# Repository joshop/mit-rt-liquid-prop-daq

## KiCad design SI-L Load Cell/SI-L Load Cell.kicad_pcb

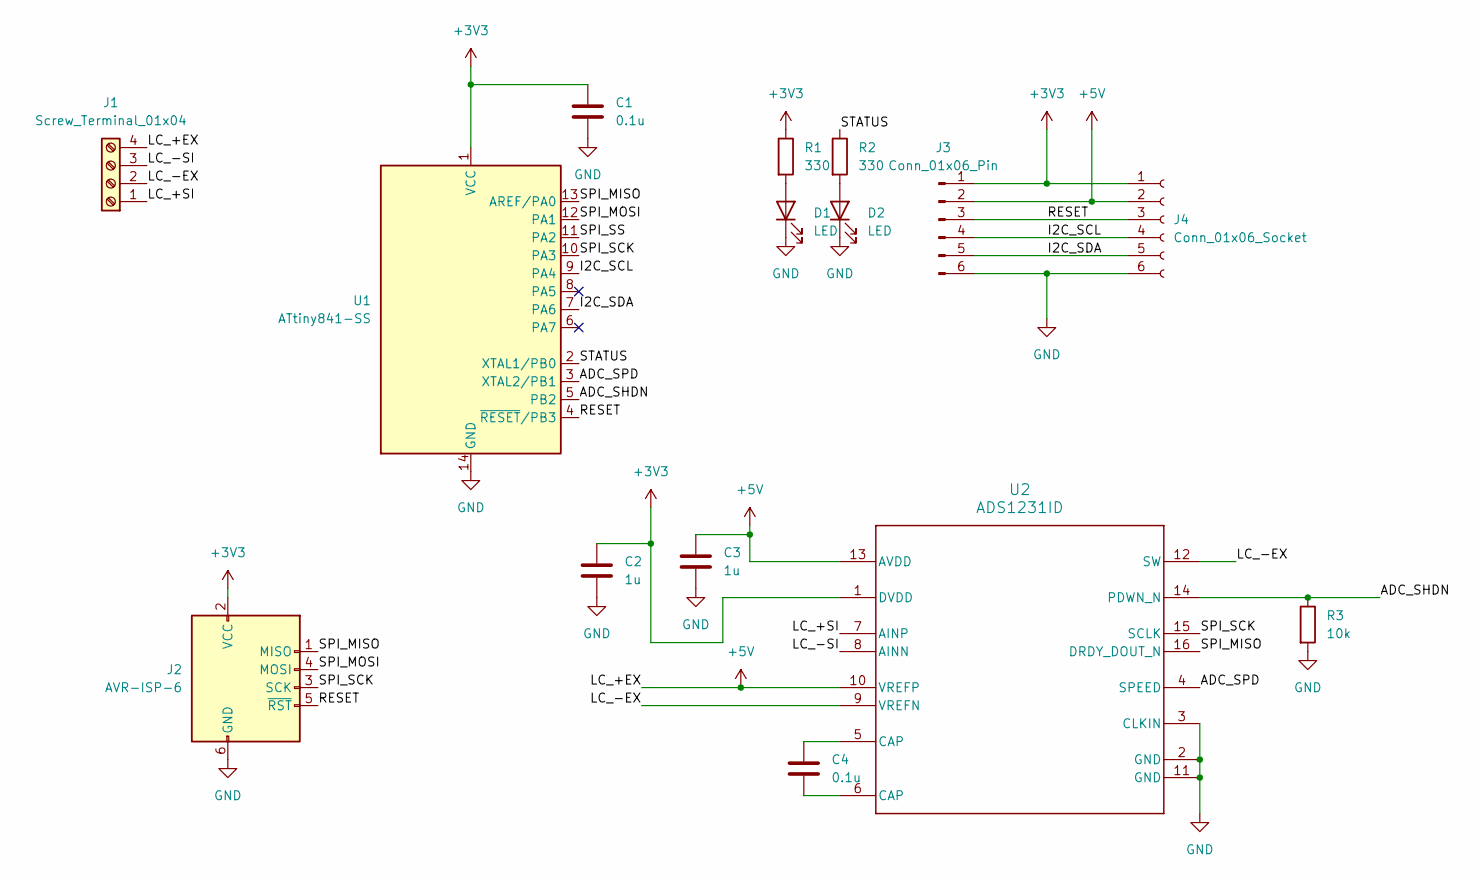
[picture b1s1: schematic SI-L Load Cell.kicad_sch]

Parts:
C1, C4: 0.1u; C_0603_1608Metric
C2, C3: 1u; C_0603_1608Metric
D1, D2: LED; LED_0603_1608Metric
J1: Screw_Terminal_01x04; TerminalBlock_Phoenix_MPT-0,5-4-2.54_1x04_P2.54mm_Horizontal
J2: AVR-ISP-6; Tag-Connect_TC2030-IDC-NL_2x03_P1.27mm_Vertical
J3: Conn_01x06_Pin; PinHeader_1x06_P2.54mm_Horizontal
J4: Conn_01x06_Socket; PinSocket_1x06_P2.54mm_Horizontal
R1, R2: 330; R_0603_1608Metric
R3: 10k; R_0603_1608Metric
U1: ATtiny841-SS; SOIC-14_3.9x8.7mm_P1.27mm
U2: ADS1231ID; D0016A_N

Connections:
+3V3: C1.1, C2.1, J2.2 (VCC), J3.1, J4.1, R1.1, U1.1 (VCC), U2.1 (DVDD)
+5V: C3.1, J1.4, J3.2, J4.2, U2.10 (VREFP), U2.13 (AVDD)
/ADC_SHDN: R3.1, U1.5 (PB2), U2.14 (PDWN_N)
/ADC_SPD: U1.3 (XTAL2/PB1), U2.4 (SPEED)
/I2C_SCL: J3.4, J4.4, U1.9 (PA4)
/I2C_SDA: J3.5, J4.5, U1.7 (PA6)
/LC_+SI: J1.1, U2.7 (AINP)
/LC_-EX: J1.2, U2.9 (VREFN), U2.12 (SW)
/LC_-SI: J1.3, U2.8 (AINN)
/RESET: J2.5 (~RST), J3.3, J4.3, U1.4 (~RESET/PB3)
/SPI_MISO: J2.1 (MISO), U1.13 (AREF/PA0), U2.16 (DRDY_DOUT_N)
/SPI_MOSI: J2.4 (MOSI), U1.12 (PA1)
/SPI_SCK: J2.3 (SCK), U1.10 (PA3), U2.15 (SCLK)
/SPI_SS: U1.11 (PA2)
/STATUS: R2.1, U1.2 (XTAL1/PB0)
GND: C1.2, C2.2, C3.2, D1.1 (K), D2.1 (K), J2.6 (GND), J3.6, J4.6, R3.2, U1.14 (GND), U2.2 (GND), U2.3 (CLKIN), U2.11 (GND)
unnamed: C4.1, U2.5 (CAP)
unnamed: C4.2, U2.6 (CAP)
unnamed: D1.2 (A), R1.2
unnamed: D2.2 (A), R2.2

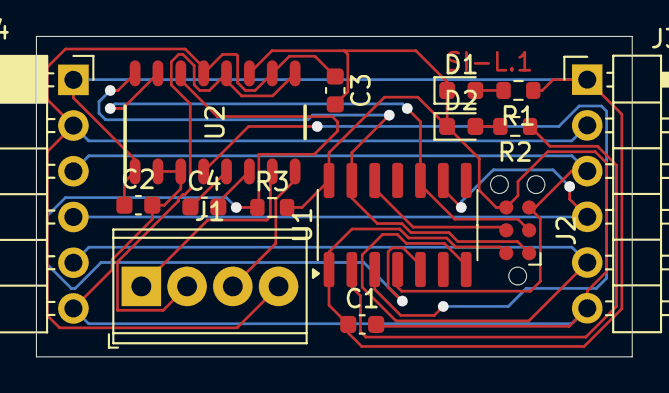
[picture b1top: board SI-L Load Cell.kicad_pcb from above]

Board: 2 copper layers, 33.1 x 17.8 mm, 15 parts (0 on the bottom side), 19 nets.

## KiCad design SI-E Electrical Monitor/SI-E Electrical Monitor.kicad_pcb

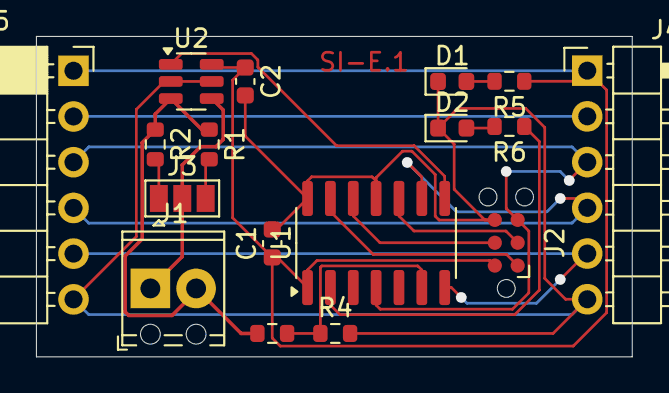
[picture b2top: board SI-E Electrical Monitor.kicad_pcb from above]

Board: 2 copper layers, 33.1 x 17.8 mm, 17 parts (0 on the bottom side), 18 nets.

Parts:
C1: 0.1u; C_0603_1608Metric
C2: C; C_0603_1608Metric
D1, D2: LED; LED_0603_1608Metric
J1: Screw_Terminal_01x02; TerminalBlock_Phoenix_MPT-0,5-2-2.54_1x02_P2.54mm_Horizontal
J2: AVR-ISP-6; Tag-Connect_TC2030-IDC-NL_2x03_P1.27mm_Vertical
J3: Conn_01x03; SolderJumper-3_P1.3mm_Open_Pad1.0x1.5mm
J4: Conn_01x06_Pin; PinHeader_1x06_P2.54mm_Horizontal
J5: Conn_01x06_Socket; PinSocket_1x06_P2.54mm_Horizontal
R1: 3m; R_0603_1608Metric
R2: 30m; R_0603_1608Metric
R3: 33k; R_0603_1608Metric
R4: 11k; R_0603_1608Metric
R5, R6: 330; R_0603_1608Metric
U1: ATtiny841-SS; SOIC-14_3.9x8.7mm_P1.27mm
U2: INA181; SOT-23-6

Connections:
+3V3: C1.1, C2.1, J2.2 (VCC), J4.1, J5.1, R5.1, U1.1 (VCC), U2.6 (V+)
+5V: J4.2, J5.2
/CS+: J1.2, R1.1, R2.1, R3.1, U2.3 (+)
/CS-: J1.1, J3.2, U2.4 (-)
/CS_OUT: U1.8 (PA5), U2.1
/I2C_SCL: J4.4, J5.4, U1.9 (PA4)
/I2C_SDA: J4.5, J5.5, U1.7 (PA6)
/RESET: J2.5 (~RST), J4.3, J5.3, U1.4 (~RESET/PB3)
/SPI_MISO: J2.1 (MISO), U1.13 (AREF/PA0)
/SPI_MOSI: J2.4 (MOSI), U1.12 (PA1)
/SPI_SCK: J2.3 (SCK), U1.10 (PA3)
/STATUS: R6.1, U1.2 (XTAL1/PB0)
GND: C1.2, C2.2, D1.1 (K), D2.1 (K), J2.6 (GND), J4.6, J5.6, R4.2, U1.11 (PA2), U1.14 (GND), U2.2 (GND), U2.5 (REF)
unnamed: D1.2 (A), R5.2
unnamed: D2.2 (A), R6.2
unnamed: J3.1, R2.2
unnamed: J3.3, R1.2
unnamed: R3.2, R4.1, U1.6 (PA7)

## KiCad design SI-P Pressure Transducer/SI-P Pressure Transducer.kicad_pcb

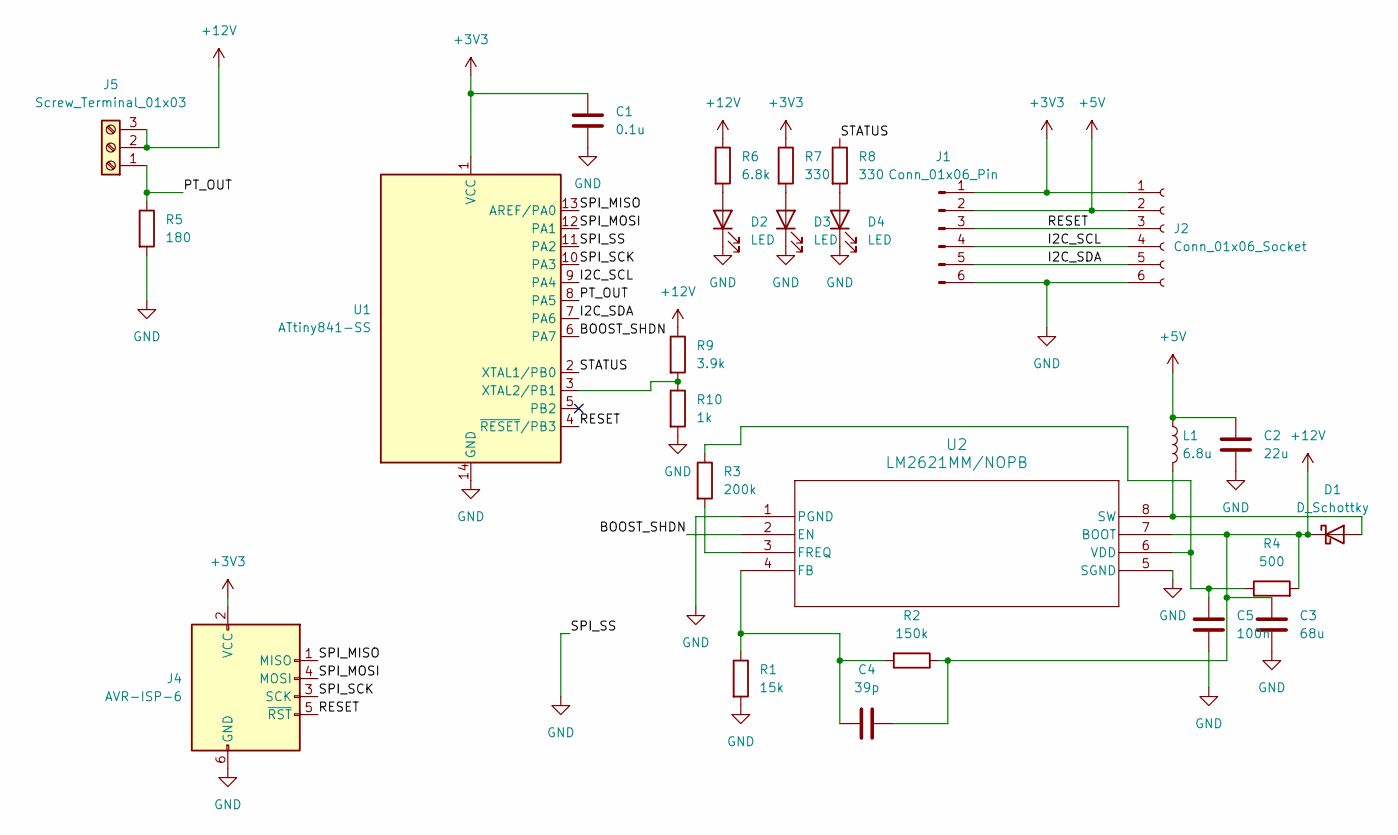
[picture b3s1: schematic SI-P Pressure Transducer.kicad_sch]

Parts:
C1: 0.1u; C_0603_1608Metric
C2: 22u; C_0603_1608Metric
C3: 68u; C_0805_2012Metric
C4: 39p; C_0603_1608Metric
C5: 100n; C_0603_1608Metric
D1: D_Schottky; D_0603_1608Metric
D2, D3, D4: LED; LED_0603_1608Metric
J1: Conn_01x06_Pin; PinHeader_1x06_P2.54mm_Horizontal
J2: Conn_01x06_Socket; PinSocket_1x06_P2.54mm_Horizontal
J4: AVR-ISP-6; Tag-Connect_TC2030-IDC-NL_2x03_P1.27mm_Vertical
J5: Screw_Terminal_01x03; TerminalBlock_Phoenix_MPT-0,5-3-2.54_1x03_P2.54mm_Horizontal
L1: 6.8u; L_0805_2012Metric
R1: 15k; R_0603_1608Metric
R2: 150k; R_0603_1608Metric
R3: 200k; R_0603_1608Metric
R4: 500; R_0603_1608Metric
R5: 180; R_0603_1608Metric
R6: 6.8k; R_0603_1608Metric
R7, R8: 330; R_0603_1608Metric
R9: 3.9k; R_0603_1608Metric
R10: 1k; R_0603_1608Metric
U1: ATtiny841-SS; SOIC-14_3.9x8.7mm_P1.27mm
U2: LM2621MM/NOPB; VSSOP-8_3x3mm_P0.65mm

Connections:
+3V3: C1.1, J1.1, J2.1, J4.2 (VCC), R7.1, U1.1 (VCC)
+5V: C2.1, J1.2, J2.2, L1.1
+12V: C3.1, C4.1, D1.1 (K), J5.2, J5.3, R2.1, R4.2, R6.1, R9.1, U2.7 (BOOT)
/BOOST_SHDN: U1.6 (PA7), U2.2 (EN)
/I2C_SCL: J1.4, J2.4, U1.9 (PA4)
/I2C_SDA: J1.5, J2.5, U1.7 (PA6)
/PT_OUT: J5.1, R5.1, U1.8 (PA5)
/RESET: J1.3, J2.3, J4.5 (~RST), U1.4 (~RESET/PB3)
/SPI_MISO: J4.1 (MISO), U1.13 (AREF/PA0)
/SPI_MOSI: J4.4 (MOSI), U1.12 (PA1)
/SPI_SCK: J4.3 (SCK), U1.10 (PA3)
/STATUS: R8.1, U1.2 (XTAL1/PB0)
GND: C1.2, C2.2, C3.2, C5.2, D2.1 (K), D3.1 (K), D4.1 (K), J1.6, J2.6, J4.6 (GND), R1.2, R5.2, R10.2, U1.11 (PA2), U1.14 (GND), U2.1 (PGND), U2.5 (SGND)
unnamed: D1.2 (A), L1.2, U2.8 (SW)
unnamed: D2.2 (A), R6.2
unnamed: D3.2 (A), R7.2
unnamed: D4.2 (A), R8.2
unnamed: R9.2, R10.1, U1.3 (XTAL2/PB1)
unnamed: C4.2, R1.1, R2.2, U2.4 (FB)
unnamed: R3.2, U2.3 (FREQ)
unnamed: C5.1, R3.1, R4.1, U2.6 (VDD)

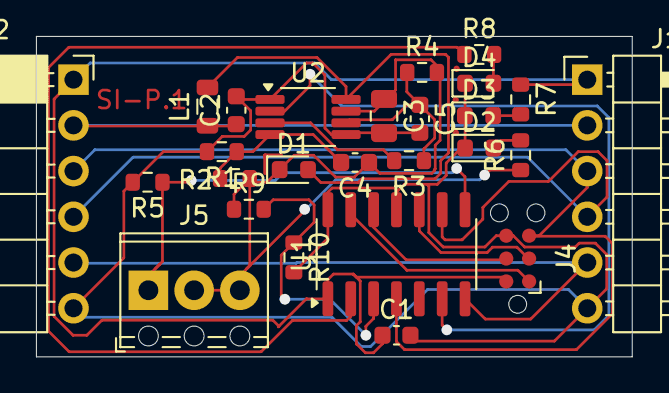
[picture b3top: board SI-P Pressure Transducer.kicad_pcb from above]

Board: 2 copper layers, 33.1 x 17.8 mm, 26 parts (0 on the bottom side), 21 nets.

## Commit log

2025-02-04 Pressure transducer board v1
2025-02-21 First revision of boards
